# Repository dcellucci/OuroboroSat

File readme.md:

#The Ouroboros Modular Satellite

 > I was sitting, writing at my text-book; but the work did not progress; my thoughts were elsewhere. I turned my chair to the fire and dozed. Again the atoms were gamboling before my eyes. This time the smaller groups kept modestly in the background. My mental eye, rendered more acute by the repeated visions of the kind, could now distinguish larger structures of manifold conformation: long rows, sometimes more closely fitted together; all twining and twisting in snake-like motion. But look! What was that? One of the snakes had seized hold of its own tail, and the form whirled mockingly before my eyes. As if by a flash of lightning I awoke; and this time also I spent the rest of the night in working out the consequences of the hypothesis.
 > ([August Kekulé](https://en.wikipedia.org/wiki/Ouroboros#Chemistry))

Ouroboros is the modular satellite platform that combines communication, power-sharing, and the Arduino framework to create a scalable platform for orbital experiments. It's designed to be even smaller than a CubeSat (one sixth, to be exact)

##What does it do?

The Ouroboros board (v. 1.0) can do alot of things. 

  1. It behaves like an Arduino, so it can run Arduino code and libraries
  2. It has the ability to charge an on-board LiPo battery from a solar panel
  3. It can connect to a maximum of four neighbors, and can talk to these four neighbors using a protocol called the Asynchronous Packet Automaton (which you can learn more about [here](https://github.com/dcellucci/APA_Tutorial)).
  4. It can also use this connection to charge a neighbor's battery using its own on-board battery, for which there are plenty of reasons, detailed in a forthcoming paper. 

Ouroboros is supposed to be alot like the Iron Man suit- it's the foundation upon which a more complex and specialized iterations can be built. My goal is to make the process of extending both the hardware and the software as easy and transparent as possible.

##Installation

You'll first want to install the software libraries- Ouroboros and its dependencies- as well as the hardware board specification. 

 * To install the software libraries, simply copy the contents of `code/libraries` folder to the `libraries` directory of your Arduino sketchbook (you might have to make it). 
 * To install the board spec, copy the contents of `code/hardware` to the `hardware` directory of the sketchbook (you might thave to make that directory as well).

Check out the [advanced installation guide](code/install.md) for a method that doesn't require copying using symbolic links (Linux/OSX only).

##Getting Started
There are plenty of ways to get started. Probably the first and best way is to make your own prototype on a breadboard, which is detailed inside the `boards/breadboard` folder. That way you can practice with the wiring and the code, as well as test what you'll need to add to the existing Ouroboros board in order to get it working with your project.

The `Blank_Example` sketch provides a bare-bones implementation of the Ouroboros functionality-

##License

<br />This work is licensed under a <a rel="license" href="http://creativecommons.org/licenses/by-sa/4.0/">Creative Commons Attribution-ShareAlike 4.0 International License</a>.

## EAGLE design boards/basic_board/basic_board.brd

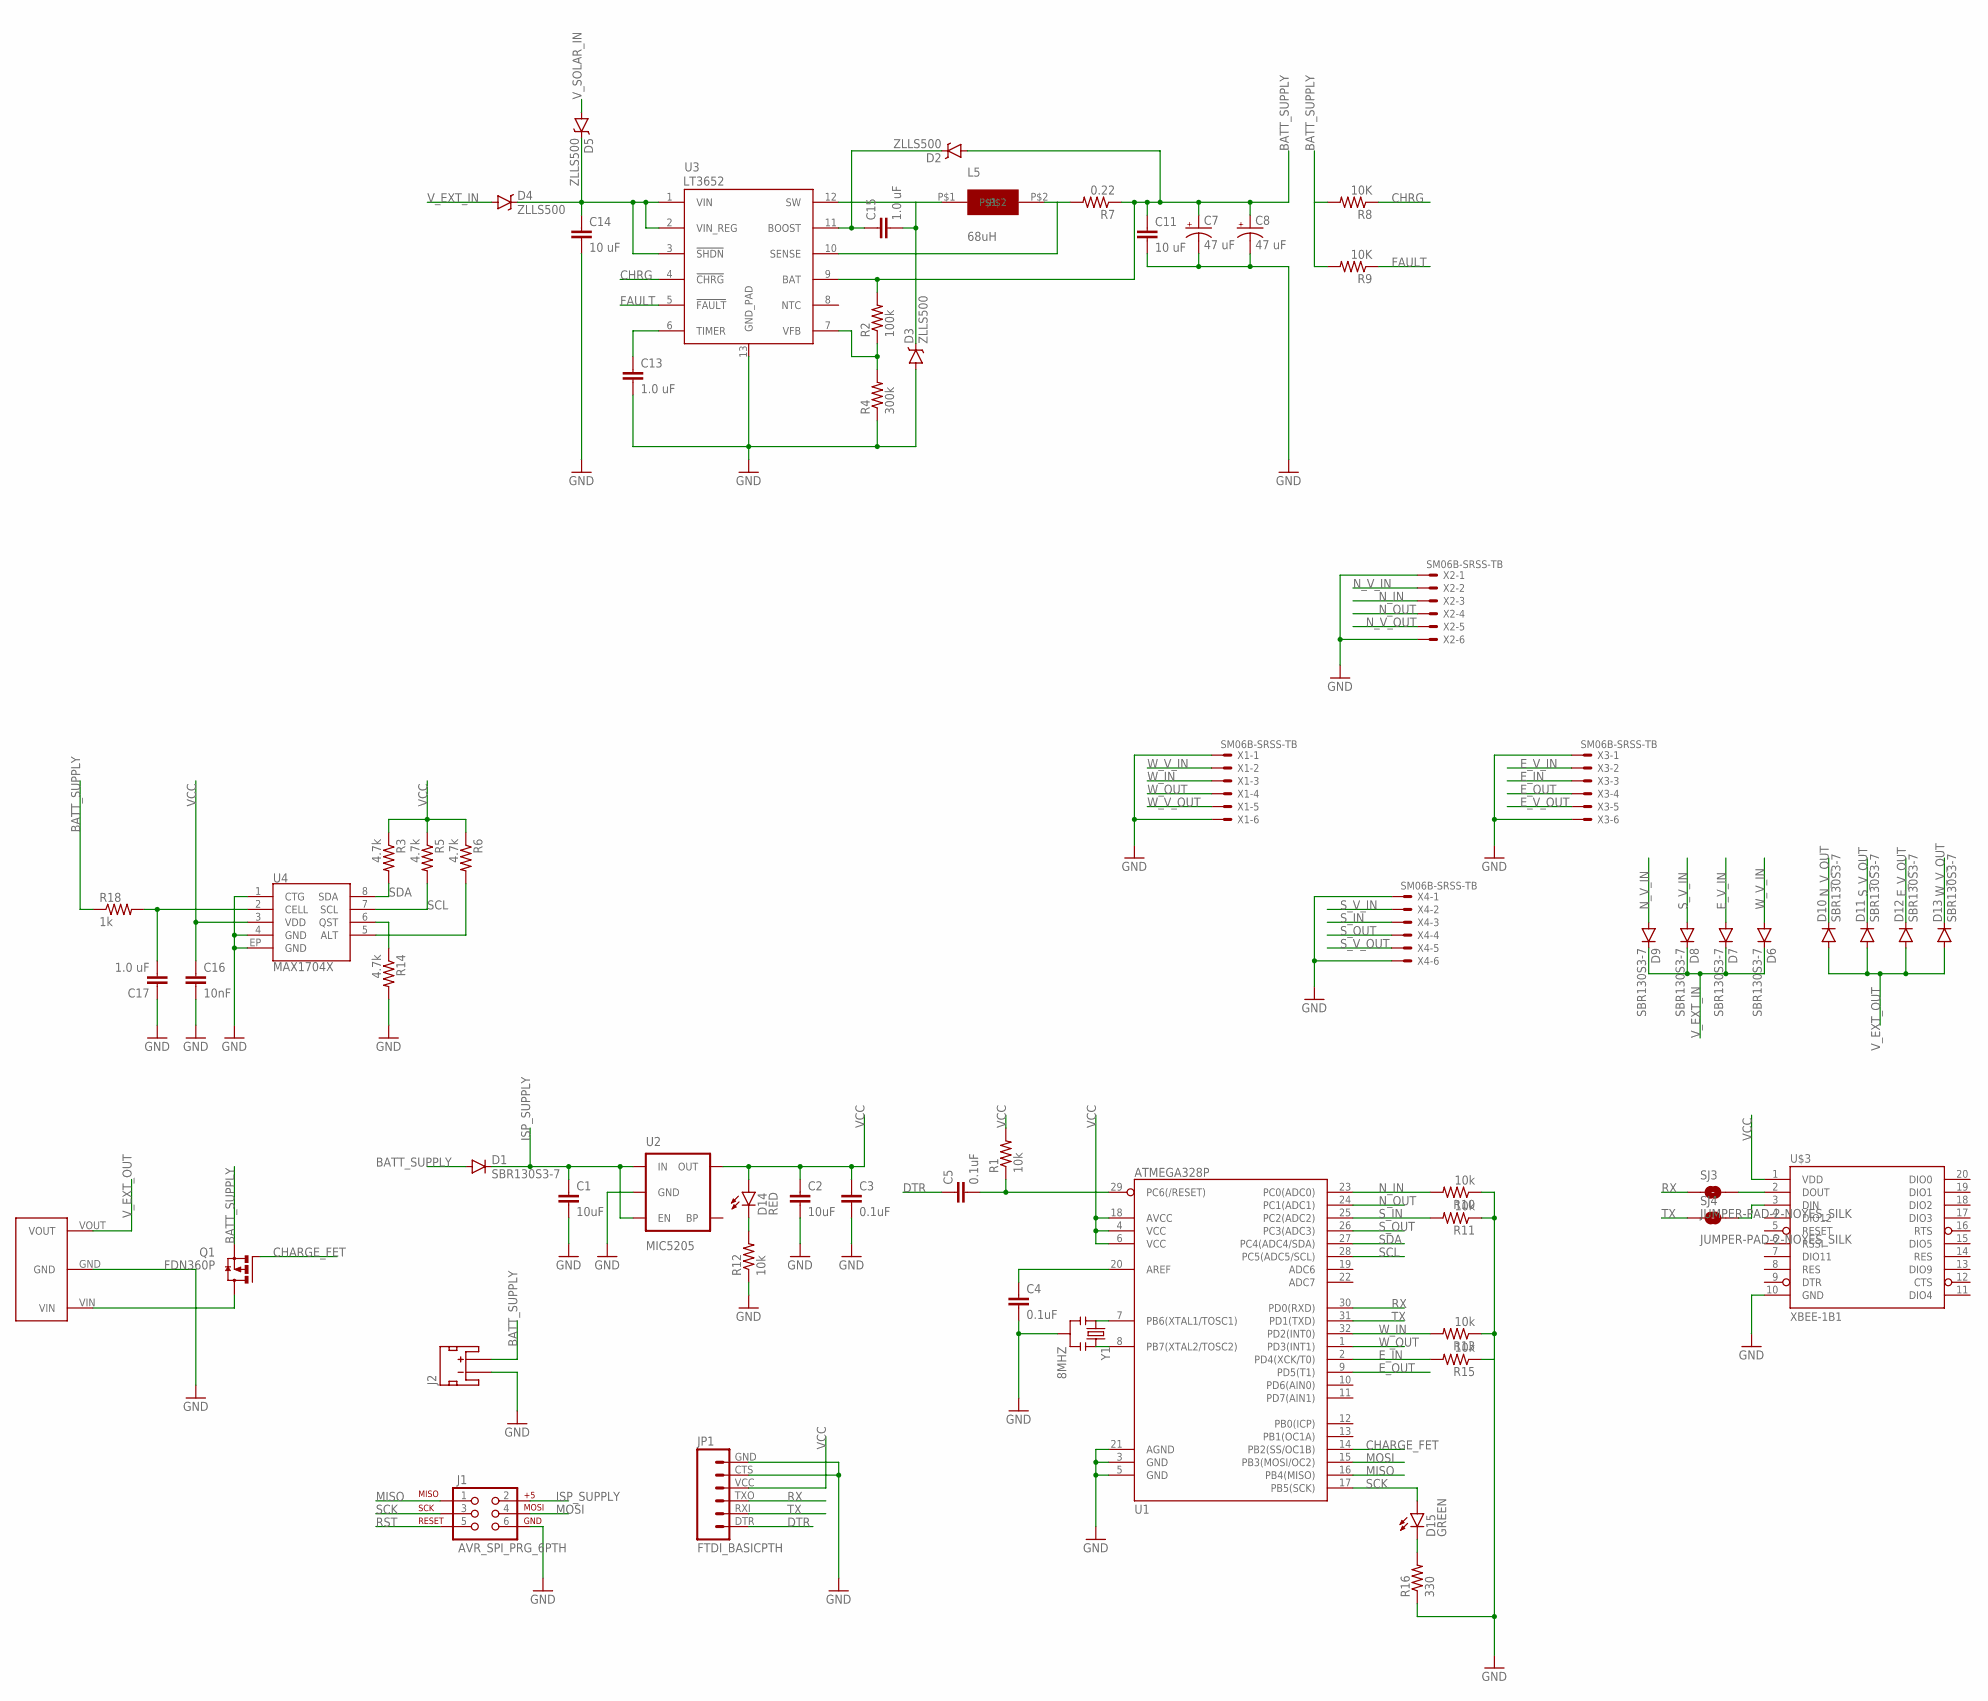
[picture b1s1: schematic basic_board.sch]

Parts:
C1, C2: 10uF; 1206
C3: 0.1uF; 1206
C4, C5: 0.1uF; 0603-CAP
C7, C8: 47 uF; EIA3216
C11, C14: 10 uF; 1206
C13, C15: 1.0 uF; 1206
C16: 10nF; 0603-CAP
C17: 1.0 uF; 0603-CAP
D1, D6, D7, D8, D9, D10, D11, D12, D13: SBR130S3-7; SOD-323
D2, D3, D4, D5: ZLLS500; SOT23
D14: RED; LED-0603
D15: GREEN; LED-0603
J1: AVR_SPI_PRG_6PTH; 2X3
J2: JST_2MM_MALE; JST-2-SMD
JP1: FTDI_BASICPTH; FTDI_BASIC
L5: 68uH; MURATA_29L68C
Q1: FDN360P; SUPER-SOT3
R1, R10, R11, R13, R15: 10k; 0603-RES
R2: 100k; 1206
R3, R5, R6, R14: 4.7k; 0603-RES
R4: 300k; 1206
R7: 0.22; 1206
R8, R9: 10K; 1206
R12: 10k; 1206
R16: 330; 1206
R18: 1k; 0603-RES
SJ3, SJ4: JUMPER-PAD-2-NOYES_SILK; PAD-JUMPER-2-NO_YES_SILK
U1: ATMEGA328P; TQFP32-08
U2: MIC5205; SOT23-5
U3: LT3652; MSOP-12_GND
U4: MAX1704X; TDFN-8
U$1: POLOLU791BOOSTPOLOLU; POLOLU791_BOOST
U$3: XBEE-1B1; XBEE-1
X1, X2, X3, X4: SM06B-SRSS-TB
Y1: 8MHZ; RESONATOR-SMD

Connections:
BATT_SUPPLY: C7.A (+), C8.A (+), C11.1, D1.A, D2.1 (A), J2.2 (+), Q1.2 (S), R2.2, R7.1, R8.2, R9.2, R18.1, U3.9 (BAT)
CHARGE_FET: Q1.1 (G), U1.14 (PB2(SS/OC1B))
CHRG: R8.1, U3.4 (!CHRG)
DTR: C5.1, JP1.DTR (1)
E_IN: R15.2, U1.2 (PD4(XCK/T0)), X3.3
E_OUT: U1.9 (PD5(T1)), X3.4
E_V_IN: D7.A, X3.2
E_V_OUT: D12.C, X3.5
FAULT: R9.1, U3.5 (!FAULT)
GND: C1.2, C2.2, C3.2, C4.2, C7.C (-), C8.C (-), C11.2, C13.2, C14.2, C16.2, C17.1, D3.1 (A), J1.6, J2.1 (-), JP1.CTS (5), JP1.GND (6), R4.1, R10.1, R11.1, R12.1, R13.1, R14.2, R15.1, R16.1, U1.3 (GND), U1.5 (GND), U1.21 (AGND), U2.2 (GND), U3.13 (GND_PAD), U4.1 (CTG), U4.4 (GND), U4.EP (GND), U$1.GND, U$3.10 (GND), X1.1, X1.6, X2.1, X2.6, X3.1, X3.6, X4.1, X4.6, Y1.2
ISP_SUPPLY: C1.1, D1.C, J1.2, U2.1 (IN), U2.3 (EN)
MISO: J1.1, U1.16 (PB4(MISO))
MOSI: J1.4, U1.15 (PB3(MOSI/OC2))
unnamed: C13.1, U3.6 (TIMER)
unnamed: L5.P$2, R7.2, U3.10 (SENSE)
unnamed: C4.1, U1.20 (AREF)
unnamed: R6.2, U4.5 (ALT)
unnamed: R2.1, R4.2, U3.7 (VFB)
unnamed: C15.1, D2.3 (C), U3.11 (BOOST)
unnamed: C15.2, D3.3 (C), L5.P$1, U3.12 (SW)
unnamed: R14.1, U4.6 (QST)
unnamed: Q1.3 (D), U$1.VIN
unnamed: U1.7 (PB6(XTAL1/TOSC1)), Y1.1
unnamed: U1.8 (PB7(XTAL2/TOSC2)), Y1.3
unnamed: C17.2, R18.2, U4.2 (CELL)
unnamed: SJ3.2, U$3.2 (DOUT)
unnamed: SJ4.2, U$3.3 (DIN)
unnamed: D14.C, R12.2
unnamed: D15.C, R16.2
unnamed: C14.1, D4.3 (C), D5.3 (C), U3.1 (VIN), U3.2 (VIN_REG), U3.3 (!SHDN)
N_IN: R10.2, U1.23 (PC0(ADC0)), X2.3
N_OUT: U1.24 (PC1(ADC1)), X2.4
N_V_IN: D9.A, X2.2
N_V_OUT: D10.C, X2.5
RST: C5.2, J1.5, R1.1, U1.29 (PC6(/RESET))
RX: JP1.TXO (3), SJ3.1, U1.30 (PD0(RXD))
SCK: D15.A, J1.3, U1.17 (PB5(SCK))
SCL: R5.2, U1.28 (PC5(ADC5/SCL)), U4.7 (SCL)
SDA: R3.2, U1.27 (PC4(ADC4/SDA)), U4.8 (SDA)
S_IN: R11.2, U1.25 (PC2(ADC2)), X4.3
S_OUT: U1.26 (PC3(ADC3)), X4.4
S_V_IN: D8.A, X4.2
S_V_OUT: D11.C, X4.5
TX: JP1.RXI (2), SJ4.1, U1.31 (PD1(TXD))
VCC: C2.1, C3.1, C16.1, D14.A, JP1.VCC (4), R1.2, R3.1, R5.1, R6.1, U1.4 (VCC), U1.6 (VCC), U1.18 (AVCC), U2.5 (OUT), U4.3 (VDD), U$3.1 (VDD)
V_EXT_IN: D4.1 (A), D6.C, D7.C, D8.C, D9.C
V_EXT_OUT: D10.A, D11.A, D12.A, D13.A, U$1.VOUT
V_SOLAR_IN: D5.1 (A)
W_IN: R13.2, U1.32 (PD2(INT0)), X1.3
W_OUT: U1.1 (PD3(INT1)), X1.4
W_V_IN: D6.A, X1.2
W_V_OUT: D13.C, X1.5

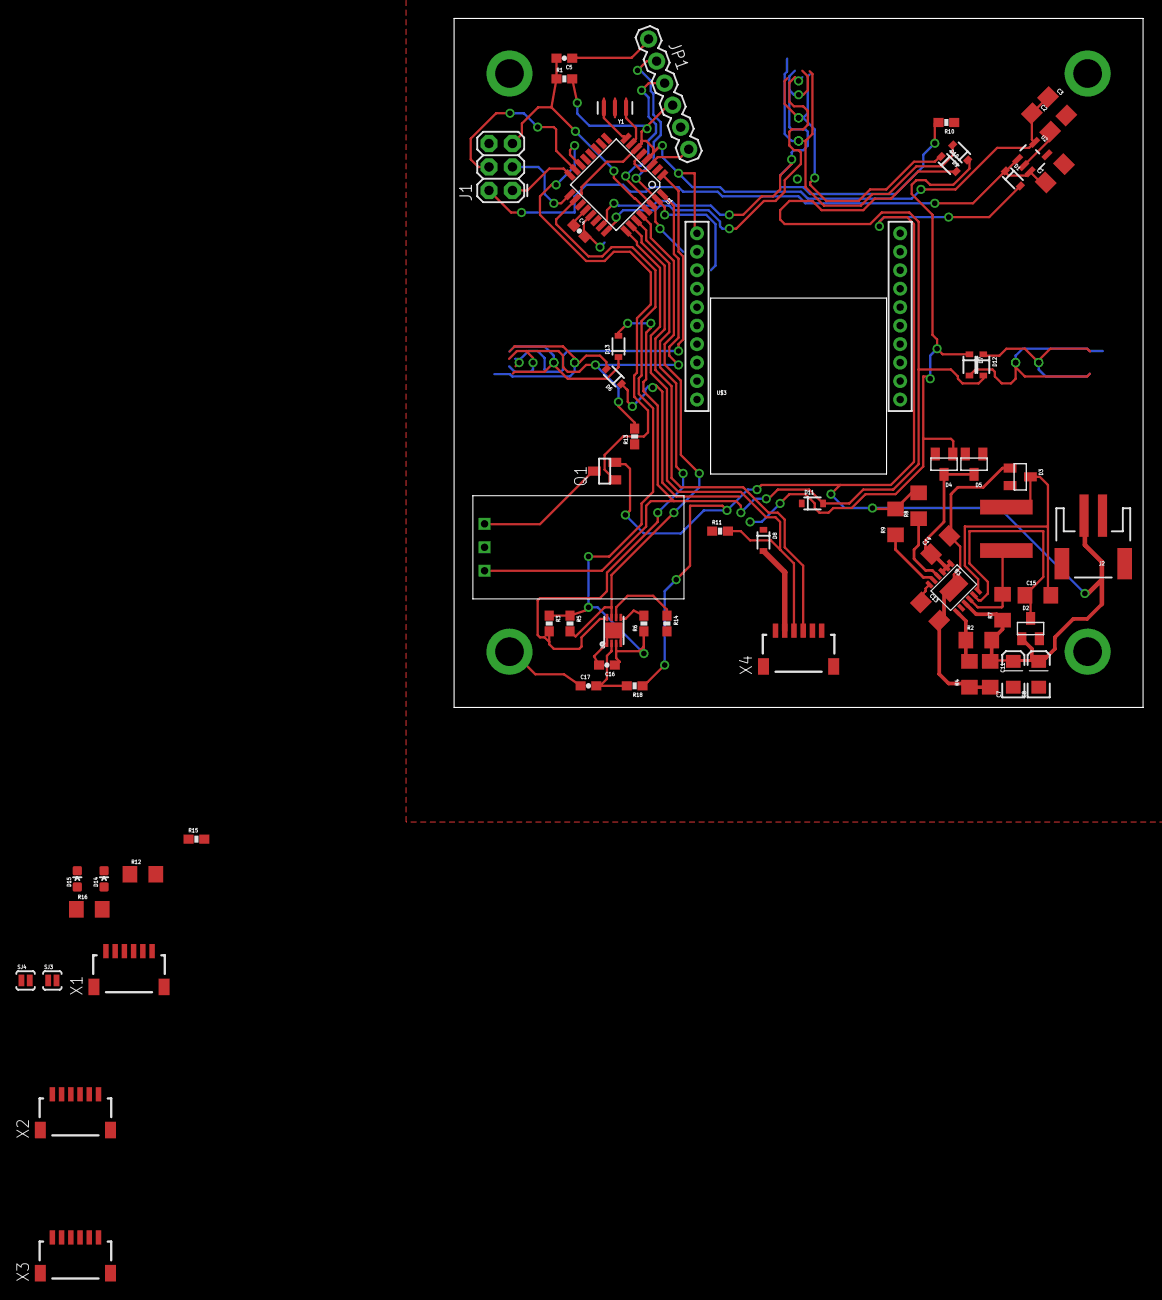
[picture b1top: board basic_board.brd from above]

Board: 2 copper layers, 74.6 x 74.6 mm, 63 parts (0 on the bottom side), 51 nets.

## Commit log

2015-01-27 The Ouroboros Satellite Board
    First Upload
2015-01-28 Added a read
2015-02-03 Cleaned Up Code
    Basically
2015-02-09 added lots of thing
    error checking functionality for lip fuel gauge
    and a blank sketch that shows how to make the barely functioning board
    work.
2015-05-26 Creating Rev 4 board
    Work In Progress - Moving away from the card edge connector
2015-05-26 Modified README
2015-05-26 Added the Card Edge Board
2015-05-26 Added Card Edge Connector
2015-05-27 Added License Info
2015-05-27 Added breadboard
    Fritzing + Readme
2015-05-27 Updated Readme's
2015-06-02 Reconfigured file layout
2015-06-02 added MAX17043 Code
2015-06-02 added MAX17043 README
2015-06-02 removed blank ouroboros from root folder
2015-06-02 added Hardware defs
2015-06-03 moving things around
2015-06-03 removed TODO
2015-07-20 Create gh-pages branch via GitHub
2015-07-20 added install + logo
2015-07-20 updated index.html
2015-07-20 trying again
2015-07-20 changing size
2015-07-20 maybe percent?
2015-07-20 index changes
2015-07-20 more index changes
2015-07-20 some more changes to index
2015-07-20 changing style + logo placement
2016-07-15 fixed APA?
2016-07-15 added readme
2016-07-15 Added hardware reference docs/models
2016-07-29 added block diagram

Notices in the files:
parts and their libraries:
SparkFun-DigitalIC: Licensing: Creative Commons ShareAlike 4.0 International - https://creativecommons.org/licenses/by-sa/4.0
